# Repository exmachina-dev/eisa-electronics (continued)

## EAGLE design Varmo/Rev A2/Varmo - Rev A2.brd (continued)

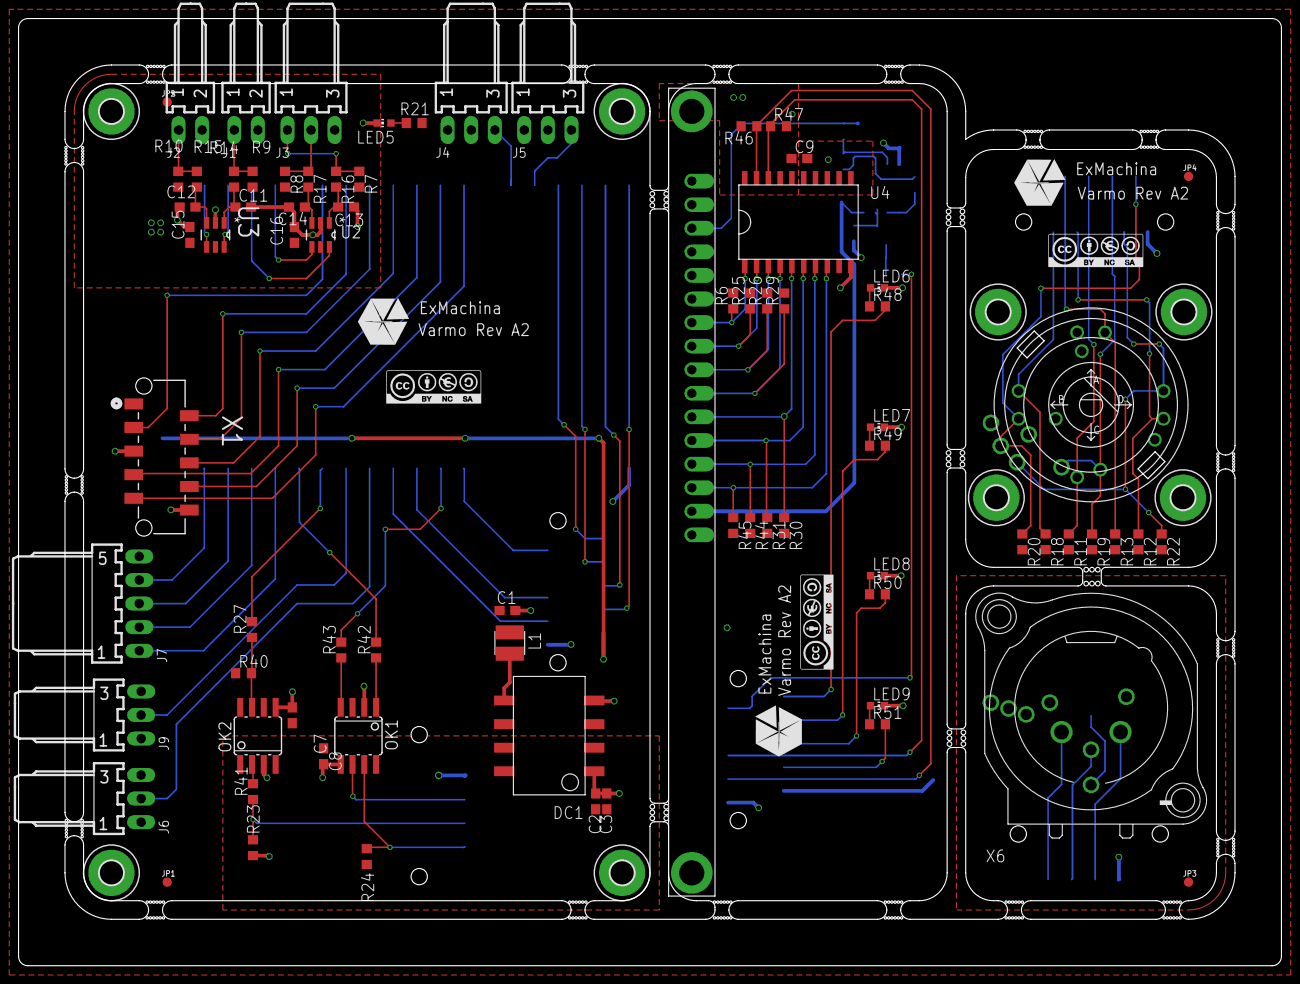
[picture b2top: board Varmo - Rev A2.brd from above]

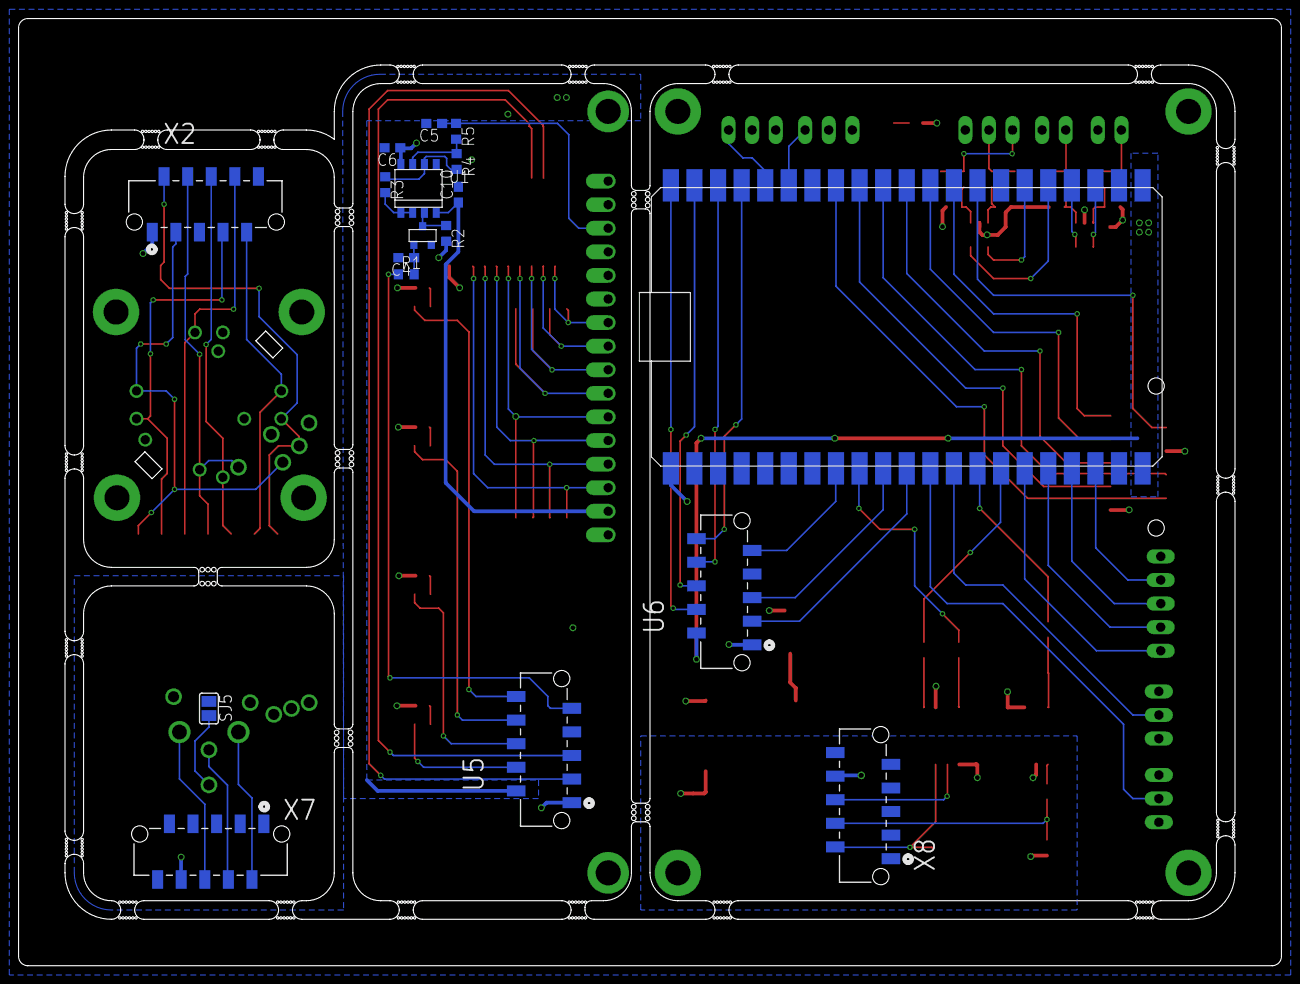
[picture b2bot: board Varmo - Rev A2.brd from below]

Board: 2 copper layers, 136.0 x 102.0 mm, 110 parts (18 on the bottom side), 74 nets.

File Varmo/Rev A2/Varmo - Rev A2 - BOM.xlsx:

Qty | Value | Device | Package | Parts | Description | MF | MPN | OC_FARNELL | OC_NEWARK | PACKAGE | SUPPLIER | VALUE
1 |  | SJ | SJ | SJ5 | SMD solder JUMPER |  |  |  | unknown
4 | 0.1uF | C-EUC0603 | C0603 | C4, C6, C9, C10 | CAPACITOR, European symbol |  | MC0603B104K160CT
9 | 0.1uF | C-EUC0603 | C0603 | C3, C7, C8, C11, C12, C13, C14, C15, C16 | CAPACITOR, European symbol |  | MC0603B104K160CT |  | 06R4923
1 | 1.5k | R-EU_R0603 | R0603 | R21 | RESISTOR, European symbol |  | MCMR06X1501FTL |  | 86T3542
1 | 100 | R-EU_R0603 | R0603 | R24 | RESISTOR, European symbol |  | MCMR06X1000FTL |  | 86T3500
1 | 100R | R-EU_R0603 | R0603 | R1 | RESISTOR, European symbol |  | MCMR06X1000FTL
1 | 10k | R-EU_R0603 | R0603 | R5 | RESISTOR, European symbol |  | MCMR06X1002FTL
7 | 1k | R-EU_R0603 | R0603 | R2, R3, R4, R48, R49, R50, R51 | RESISTOR, European symbol |  | MCMR06X1001FTL
4 | 1k | R-EU_R0603 | R0603 | R14, R15, R16, R17 | RESISTOR, European symbol |  | MCMR06X1001FTL |  | 86T3649
2 | 1k5 | R-EU_R0603 | R0603 | R27, R41 | RESISTOR, European symbol |  | MCMR06X1501FTL |  | 86T3500
2 | 22-05-7028-02 | 22-05-7028-02 |  | J1, J2 | CONNECTOR |  | 22-02-7038 | 9731601 | unknown
5 | 22-05-7038-03 | 22-05-7038-03 |  | J3, J4, J5, J6, J9 | CONNECTOR |  | 22-02-7038 | 9731610 | unknown
1 | 22-05-7058-05 | 22-05-7058-05 |  | J7 | CONNECTOR |  | 22-05-7038 | 9731636 | unknown
2 | 330 | R-EU_R0603 | R0603 | R42, R43 | RESISTOR, European symbol |  | MCMR06X3300FTL |  | 86T3500
1 | 4.7K | R-EU_R0603 | R0603 | R8 | RESISTOR, European symbol |  | MCMR06X4701FTL |  | 86T3649
10 | 4.7k | R-EU_R0603 | R0603 | R6, R25, R26, R29, R30, R31, R44, R45, R46, R47 | RESISTOR, European symbol |  | MCMR06X4701FTL
3 | 4.7k | R-EU_R0603 | R0603 | R7, R9, R10 | RESISTOR, European symbol |  | MCMR06X4701FTL |  | 86T3649
1 | 4.7uF | C-EUC0603 | C0603 | C5 | CAPACITOR, European symbol |  | MC0603X475K100CT
2 | 4.7uF | C-EUC0603 | C0603 | C1, C2 | CAPACITOR, European symbol |  | MC0603X475K100CT |  | 06X6198
1 | 47uH | 82473C | 8200 | L1 |  |  | 82473C |  | 40M7122 |  |  | 47uH
9 | 4k7 | R-EU_R0603 | R0603 | R11, R12, R13, R18, R19, R20, R22, R23, R40 | RESISTOR, European symbol |  | MCMR06X4701FTL |  | 86T3500
6 | 90814-0210 | 90814-0210 | MOLEX_90814-0210 | U5, U6, X1, X2, X7, X8 | CONN HEADER 10POS 1.27MM SMD TIN |  | 90814-0210 | 1757026 | 34R6217 | CONN-10POS | Molex
4 | Blue | LEDCHIP-LED0603 | CHIP-LED0603 | LED6, LED7, LED8, LED9 | LED |  | OVS-0603
3 | CC-BY-NC-SA | CC-BY-NC-SA | CC-BY-NC-SA | U$1, U$4, U$5
1 | EC20AE | EC20AE | EC20A | U$2 |  |  | EC20A1824401
3 | EXMACHINA-LOGO-NAME | EXMACHINA-LOGO-NAME | EXM-LOGO-BASELINE | U$3, U$6, U$7
4 | FIDUCIAL1X2 | FIDUCIAL1X2 | FIDUCIAL-1X2 | JP1, JP2, JP3, JP4 | Fiducial Alignment Points
1 | Green | LEDCHIP-LED0603 | CHIP-LED0603 | LED5 | LED |  | OVS-0604 |  | 15R2206
1 | HCPL0201 | HCPL0201 | SOIC08 | OK2 |  |  | HCPL-0201-500E
1 | HCPL0631 | HCPL0631 | SOIC08 | OK1 |  |  | HCPL-0631-500E
1 | LT1813CS8 | LT1813CS8 | SOIC8 | U1 | Dual AOP 3mA, 100MHz, 750V/us |  | LT1813CS8#PBF
1 | M20DX256 | M20DX256 | MK_CUSTOM | U8
1 | MC41605A12W | MC41605A12W | CONNECTOR | LCD1 |  |  | MC41605A12W-VNMLW
1 | MMBT2222AL | MMBT2222AL | SOT-23 | T1 | General Purpose Transistors |  | MMBT2222ALT1G
8 | MOUNT-PAD2.5 | MOUNT-PAD2.5 | P2.5 | MP1, MP2, MP3, MP4, MP5, MP6, MP7, MP8 | MOUNTING HOLE with drill center marker
1 | NC5MAV-SW | NC5MAV-SW | NC5MAV-SW | X6 | Neutrik Audio Connector XLR SERIES |  | NC5MAV-SW | unknown | 31M5714
1 | NTE0505MC | NTE0505MC | NTE | DC1 |  | C & D TECHNOLOGIES, INC | NTE0505MC |  | 61K3399
1 | PCA9665D | PCA9665D | SOT163-1 | U4
1 | RKJXTF42001 | RKJXTF42001 | RKJXT1F | ENC1 | 4-directional Stick Switch (with Encoder + Center-push Function)
2 | SN74LVC2G17DBVR | SN74LVC2G17DBVR | SOT95P280X145-6N | U2, U3 | DUAL SCHMITT-TRIGGER BUFFER | TEXAS INSTRUMENTS | SN74LVC2G17DBVR | 1470776 | 76C4207 | SOT-23-6 | Texas Instruments

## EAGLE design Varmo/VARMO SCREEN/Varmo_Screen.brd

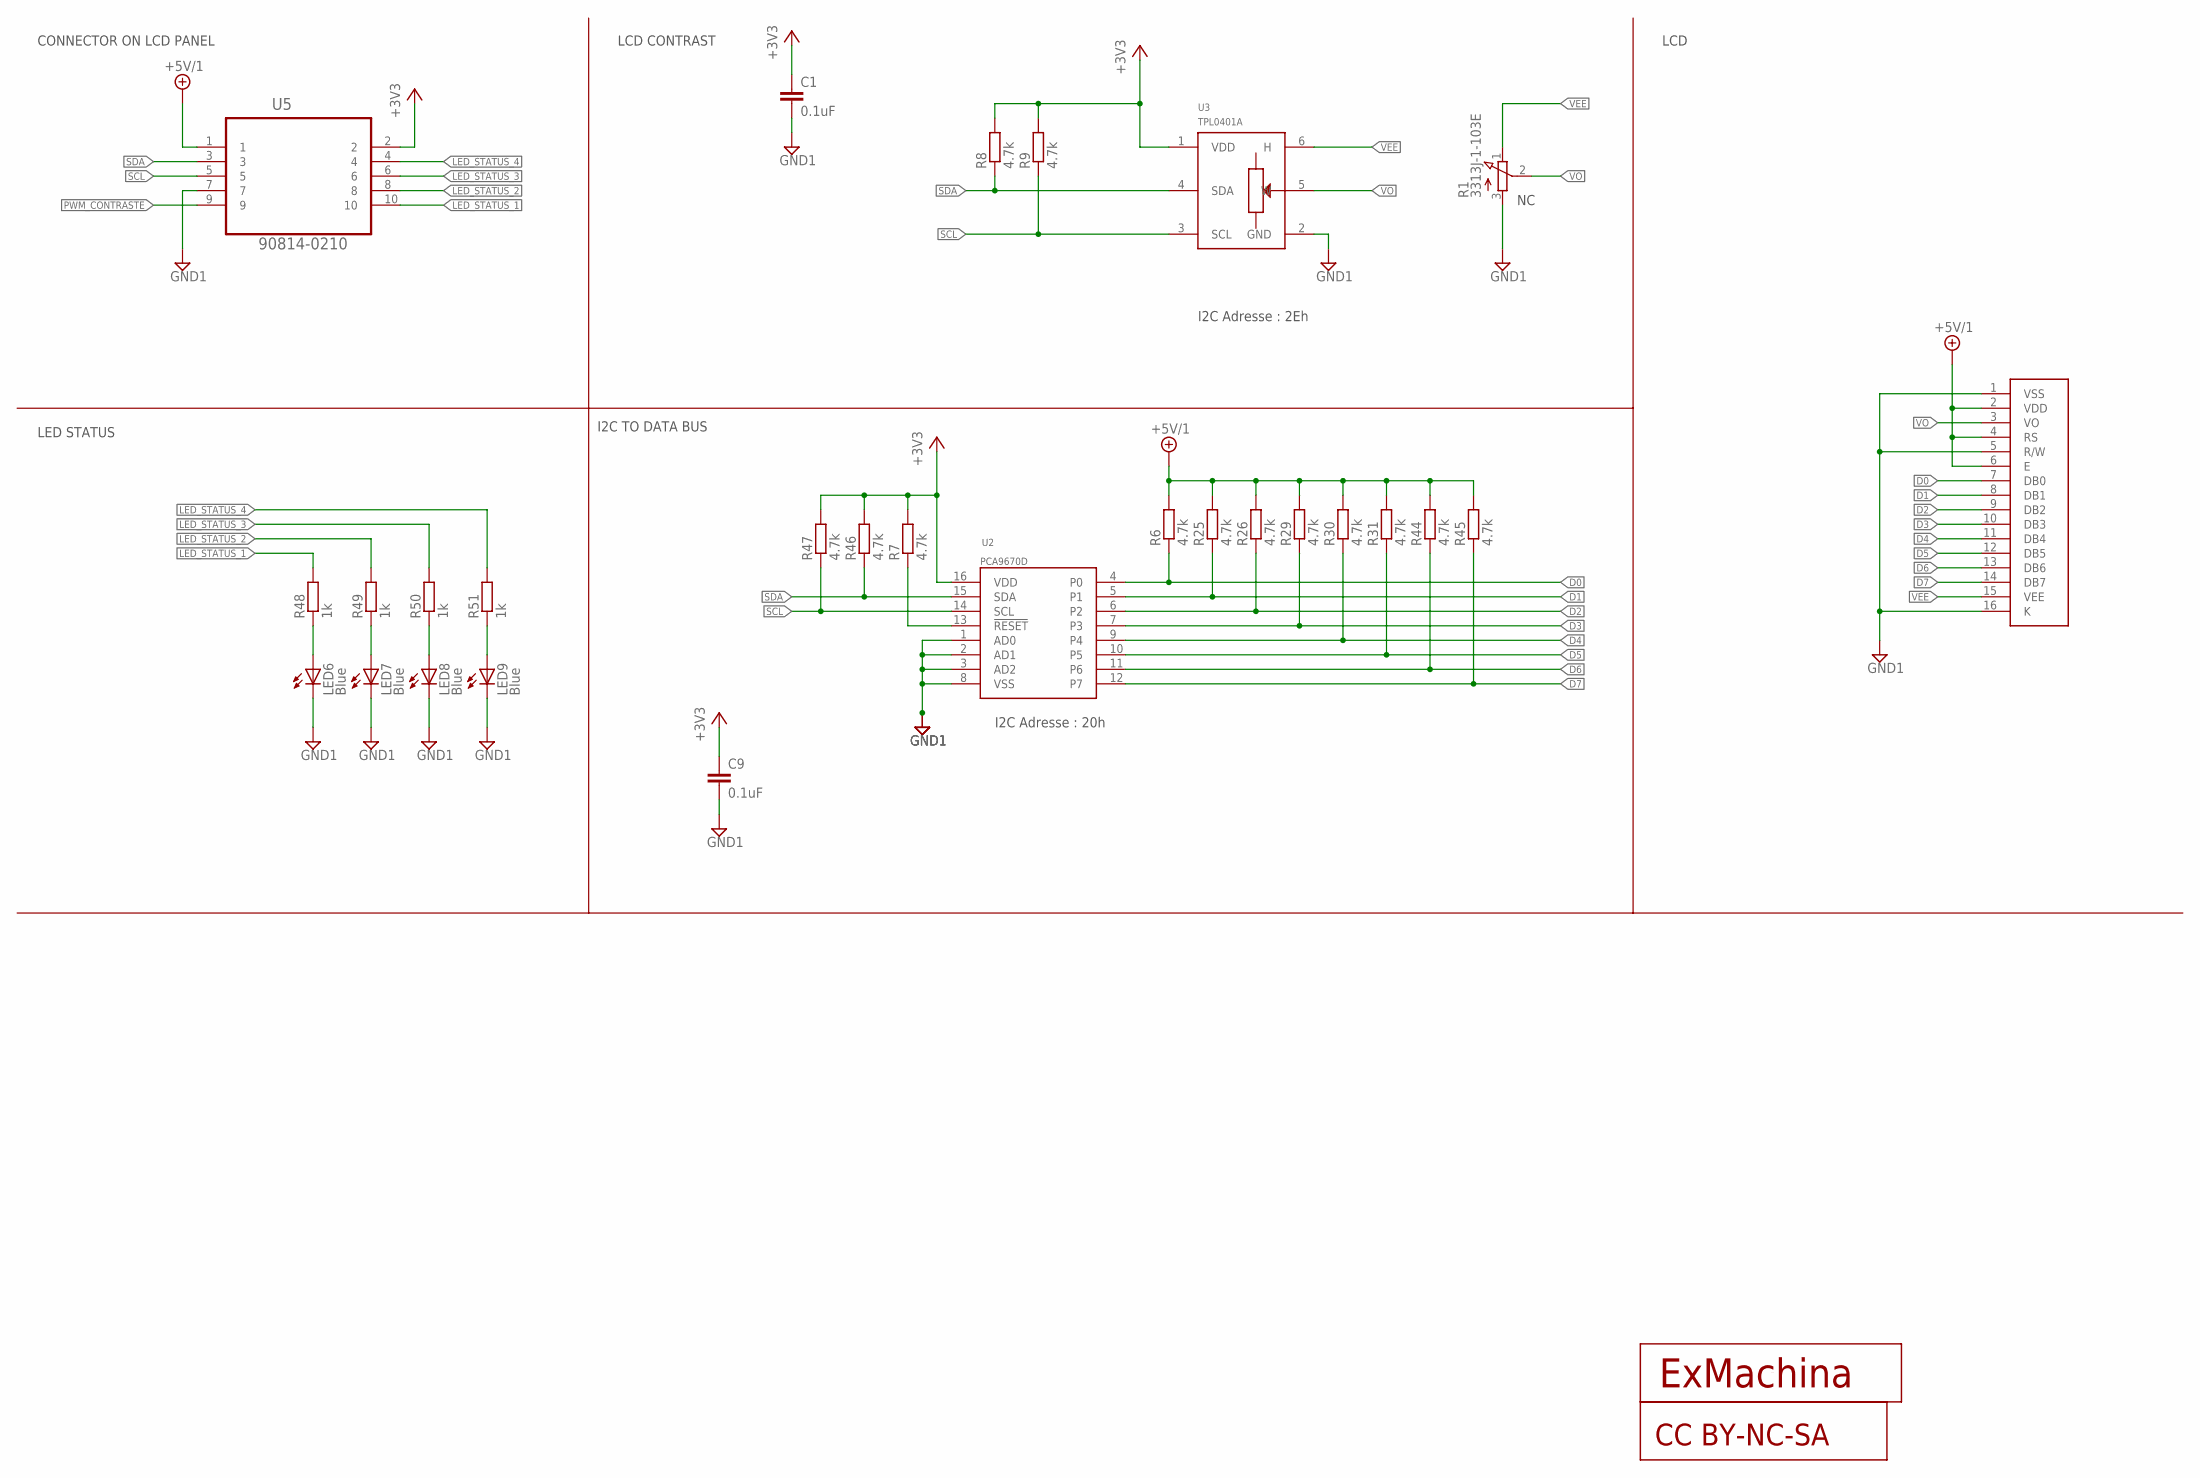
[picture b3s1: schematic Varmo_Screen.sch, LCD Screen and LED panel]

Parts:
C1, C9: 0.1uF; C0603
LCD1: MC41605A12W; CONNECTOR
LED6, LED7, LED8, LED9: Blue; CHIP-LED0603
R1: 3313J-1-103E; 3313J
R6, R7, R8, R9, R25, R26, R29, R30, R31, R44, R45, R46, R47: 4.7k; R0603
R48, R49, R50, R51: 1k; R0603
U2: PCA9670D; SOT162-1
U3: TPL0401A; SC-70-DCK
U5: 90814-0210; MOLEX_90814-0210
U$5: CC-BY-NC-SA
U$7: EXMACHINA-LOGO-NAME; EXM-LOGO-BASELINE

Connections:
+3V3: C1.1, C9.1, R7.2, R8.2, R9.2, R46.2, R47.2, U2.16 (VDD), U3.1 (VDD), U5.2
+5V/1: LCD1.2 (VDD), LCD1.4 (RS), LCD1.6 (E), R6.2, R25.2, R26.2, R29.2, R30.2, R31.2, R44.2, R45.2, U5.1
D0: LCD1.7 (DB0), R6.1, U2.4 (P0)
D1: LCD1.8 (DB1), R25.1, U2.5 (P1)
D2: LCD1.9 (DB2), R26.1, U2.6 (P2)
D3: LCD1.10 (DB3), R29.1, U2.7 (P3)
D4: LCD1.11 (DB4), R30.1, U2.9 (P4)
D5: LCD1.12 (DB5), R31.1, U2.10 (P5)
D6: LCD1.13 (DB6), R44.1, U2.11 (P6)
D7: LCD1.14 (DB7), R45.1, U2.12 (P7)
GND1: C1.2, C9.2, LCD1.1 (VSS), LCD1.5 (R/W), LCD1.16 (K), LED6.C, LED7.C, LED8.C, LED9.C, R1.3 (A), U2.1 (AD0), U2.2 (AD1), U2.3 (AD2), U2.8 (VSS), U3.2 (GND), U5.7
LED_STATUS_1: R48.2, U5.10
LED_STATUS_2: R49.2, U5.8
LED_STATUS_3: R50.2, U5.6
LED_STATUS_4: R51.2, U5.4
unnamed: R7.1, U2.13 (!RESET)
unnamed: LED6.A, R48.1
unnamed: LED7.A, R49.1
unnamed: LED8.A, R50.1
unnamed: LED9.A, R51.1
PWM_CONTRASTE: U5.9
SCL: R9.1, R47.1, U2.14 (SCL), U3.3 (SCL), U5.5
SDA: R8.1, R46.1, U2.15 (SDA), U3.4 (SDA), U5.3
VEE: LCD1.15 (VEE), R1.1 (E), U3.6 (H)
VO: LCD1.3 (VO), R1.2 (S), U3.5 (W)

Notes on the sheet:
LCD CONTRAST
CONNECTOR ON LCD PANEL
LED STATUS
I2C TO DATA BUS
LCD
I2C Adresse : 20h
I2C Adresse : 2Eh

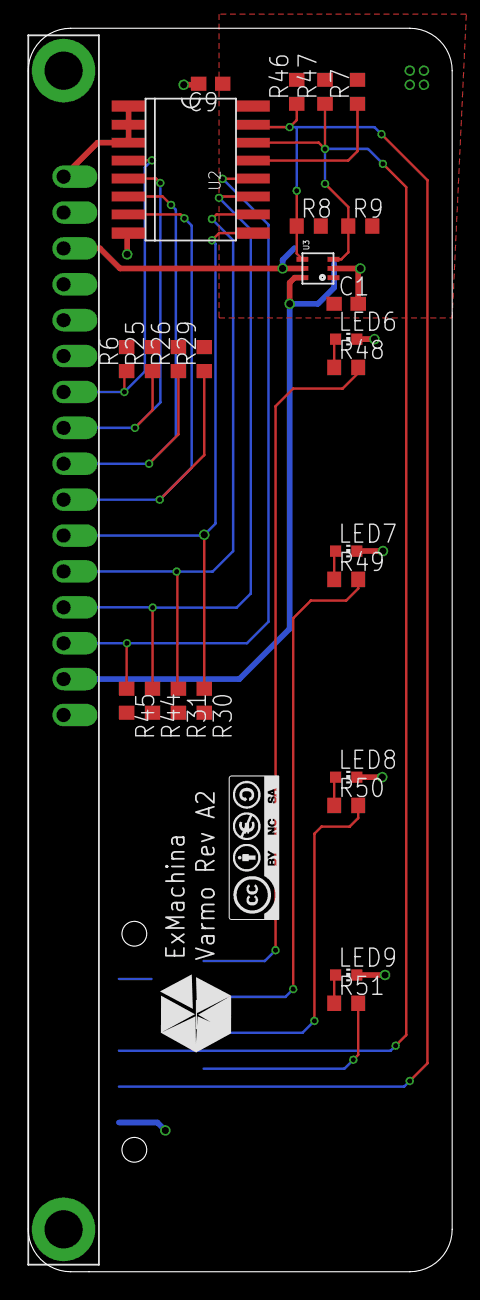
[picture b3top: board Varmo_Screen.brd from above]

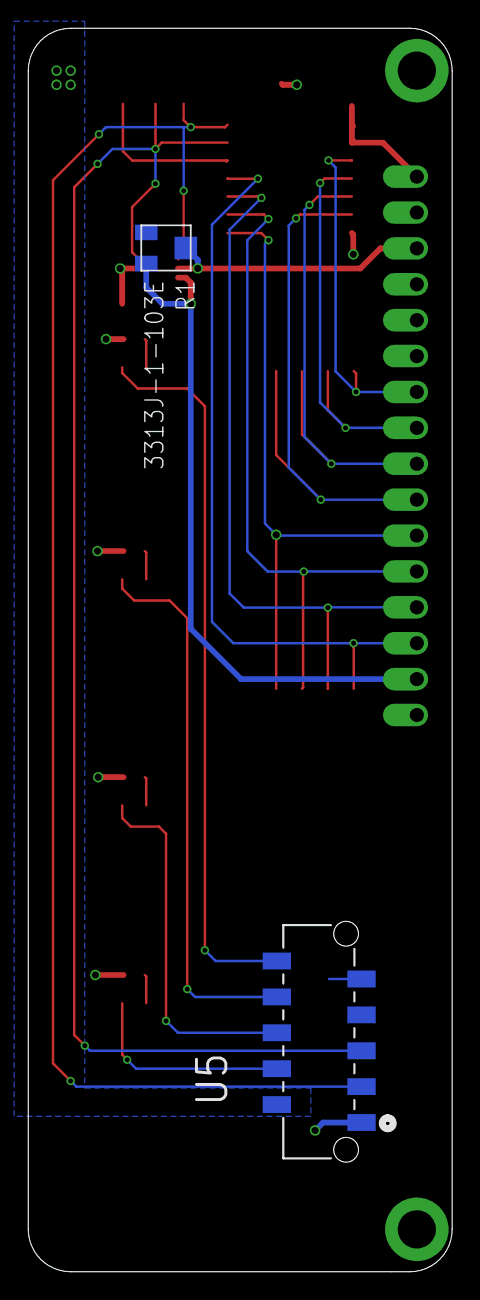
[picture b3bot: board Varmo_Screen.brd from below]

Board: 2 copper layers, 30.0 x 88.0 mm, 30 parts (2 on the bottom side), 24 nets.

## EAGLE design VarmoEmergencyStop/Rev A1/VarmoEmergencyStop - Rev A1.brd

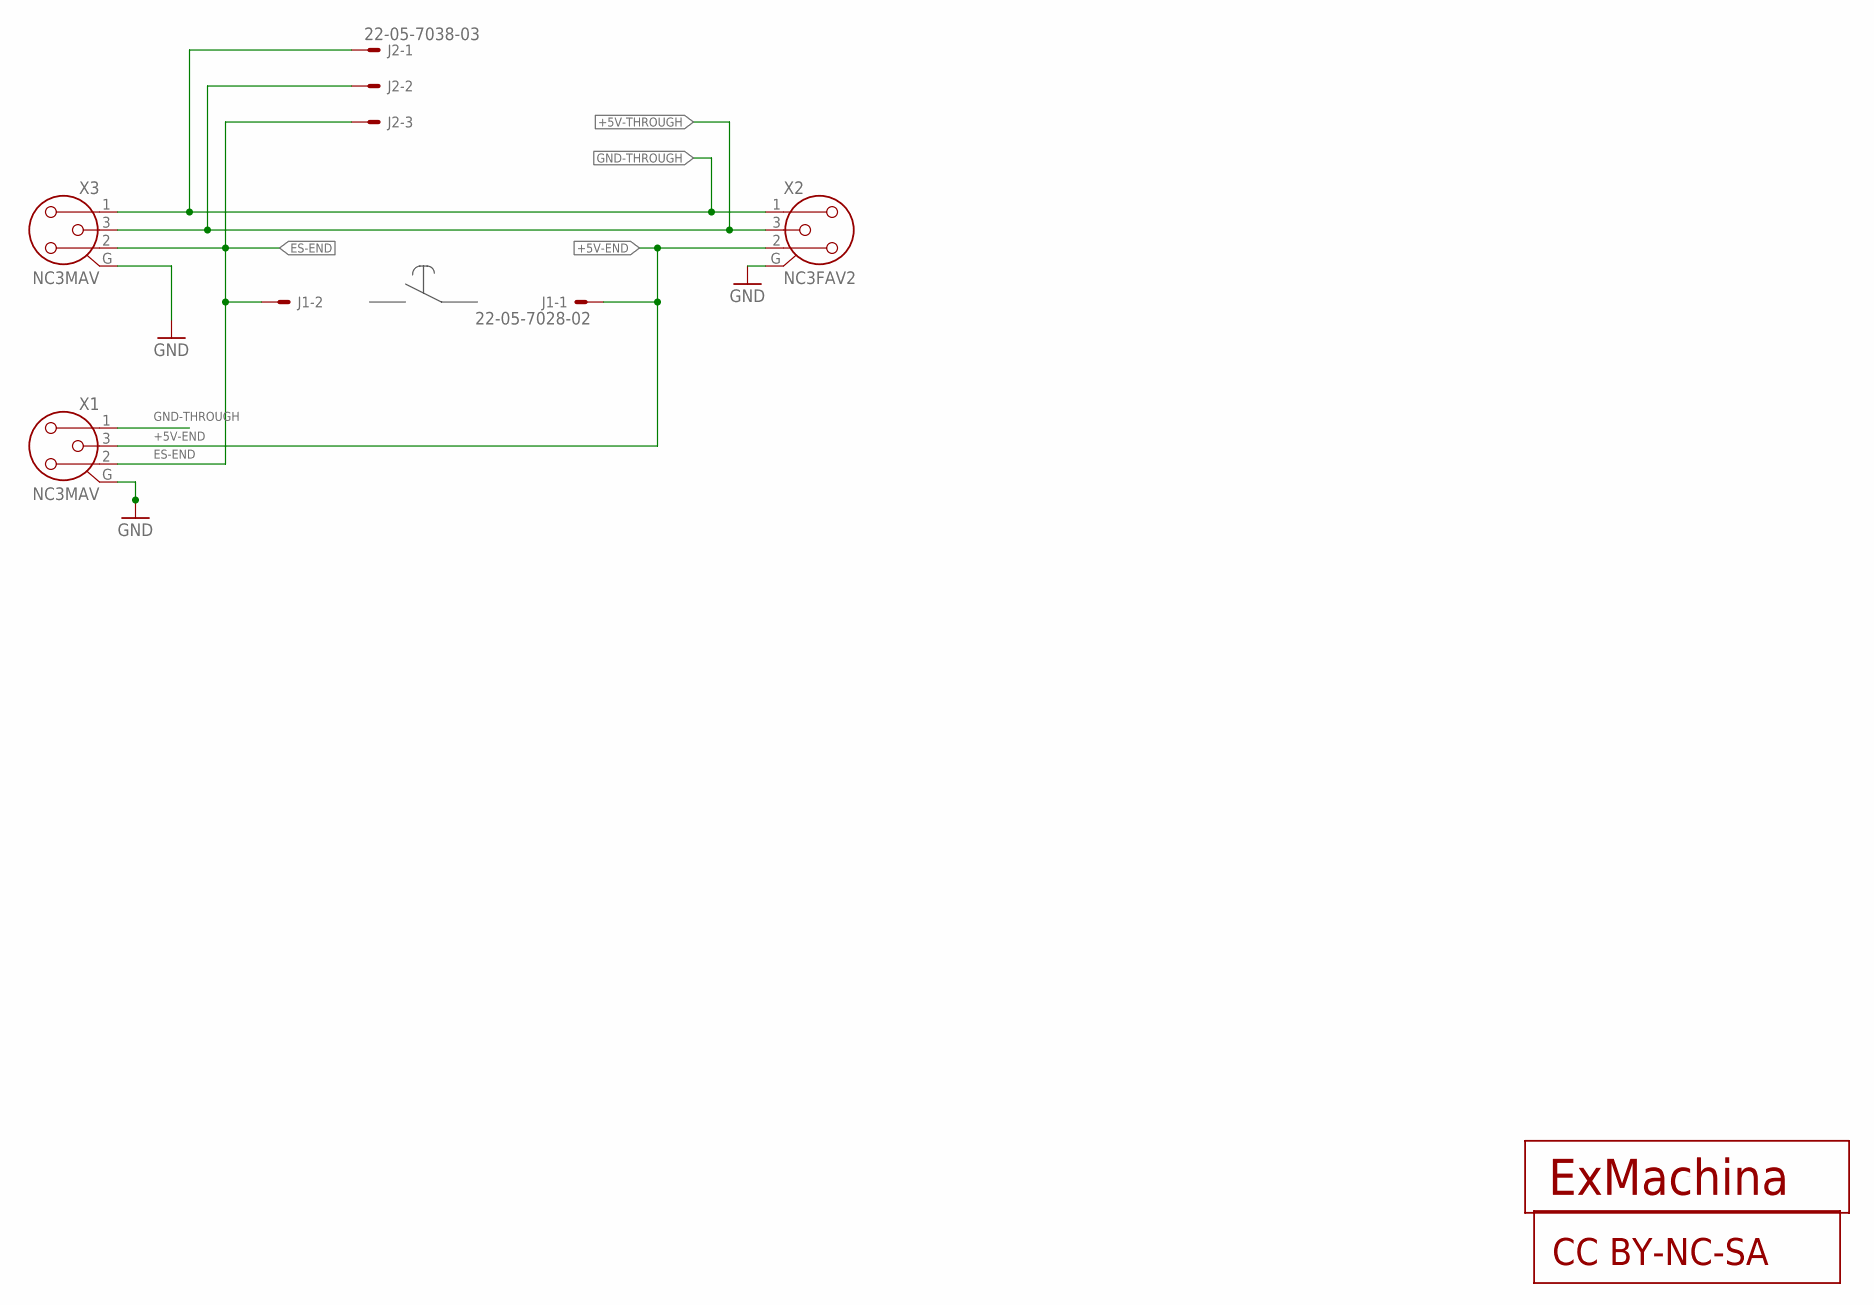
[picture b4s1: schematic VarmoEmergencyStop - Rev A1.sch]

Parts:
J1: 22-05-7028-02; 7395-02
J2: 22-05-7038-03; 7395-03
U$1: EXMACHINA-LOGO-NAME; EXM-LOGO-BASELINE
U$2: CC-BY-NC-SA
X1, X3: NC3MAV
X2: NC3FAV2

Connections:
+5V-END: J1.1, X1.3, X2.2
+5V-THROUGH: J2.2, X2.3, X3.3
ES-END: J1.2, J2.3, X1.2, X3.2
GND: X1.G, X2.G, X3.G
GND-THROUGH: J2.1, X1.1, X2.1, X3.1

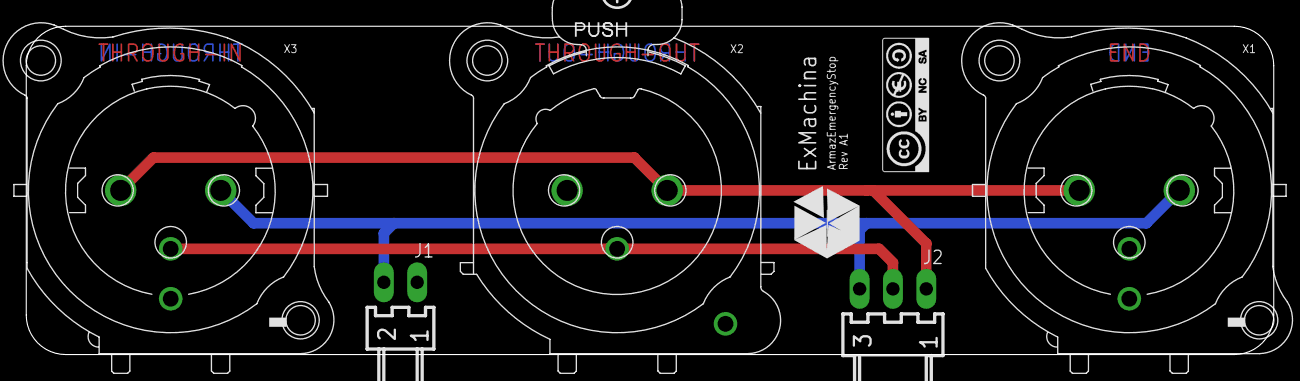
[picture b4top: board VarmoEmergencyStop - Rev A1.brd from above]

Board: 2 copper layers, 95.0 x 25.0 mm, 7 parts (0 on the bottom side), 5 nets.

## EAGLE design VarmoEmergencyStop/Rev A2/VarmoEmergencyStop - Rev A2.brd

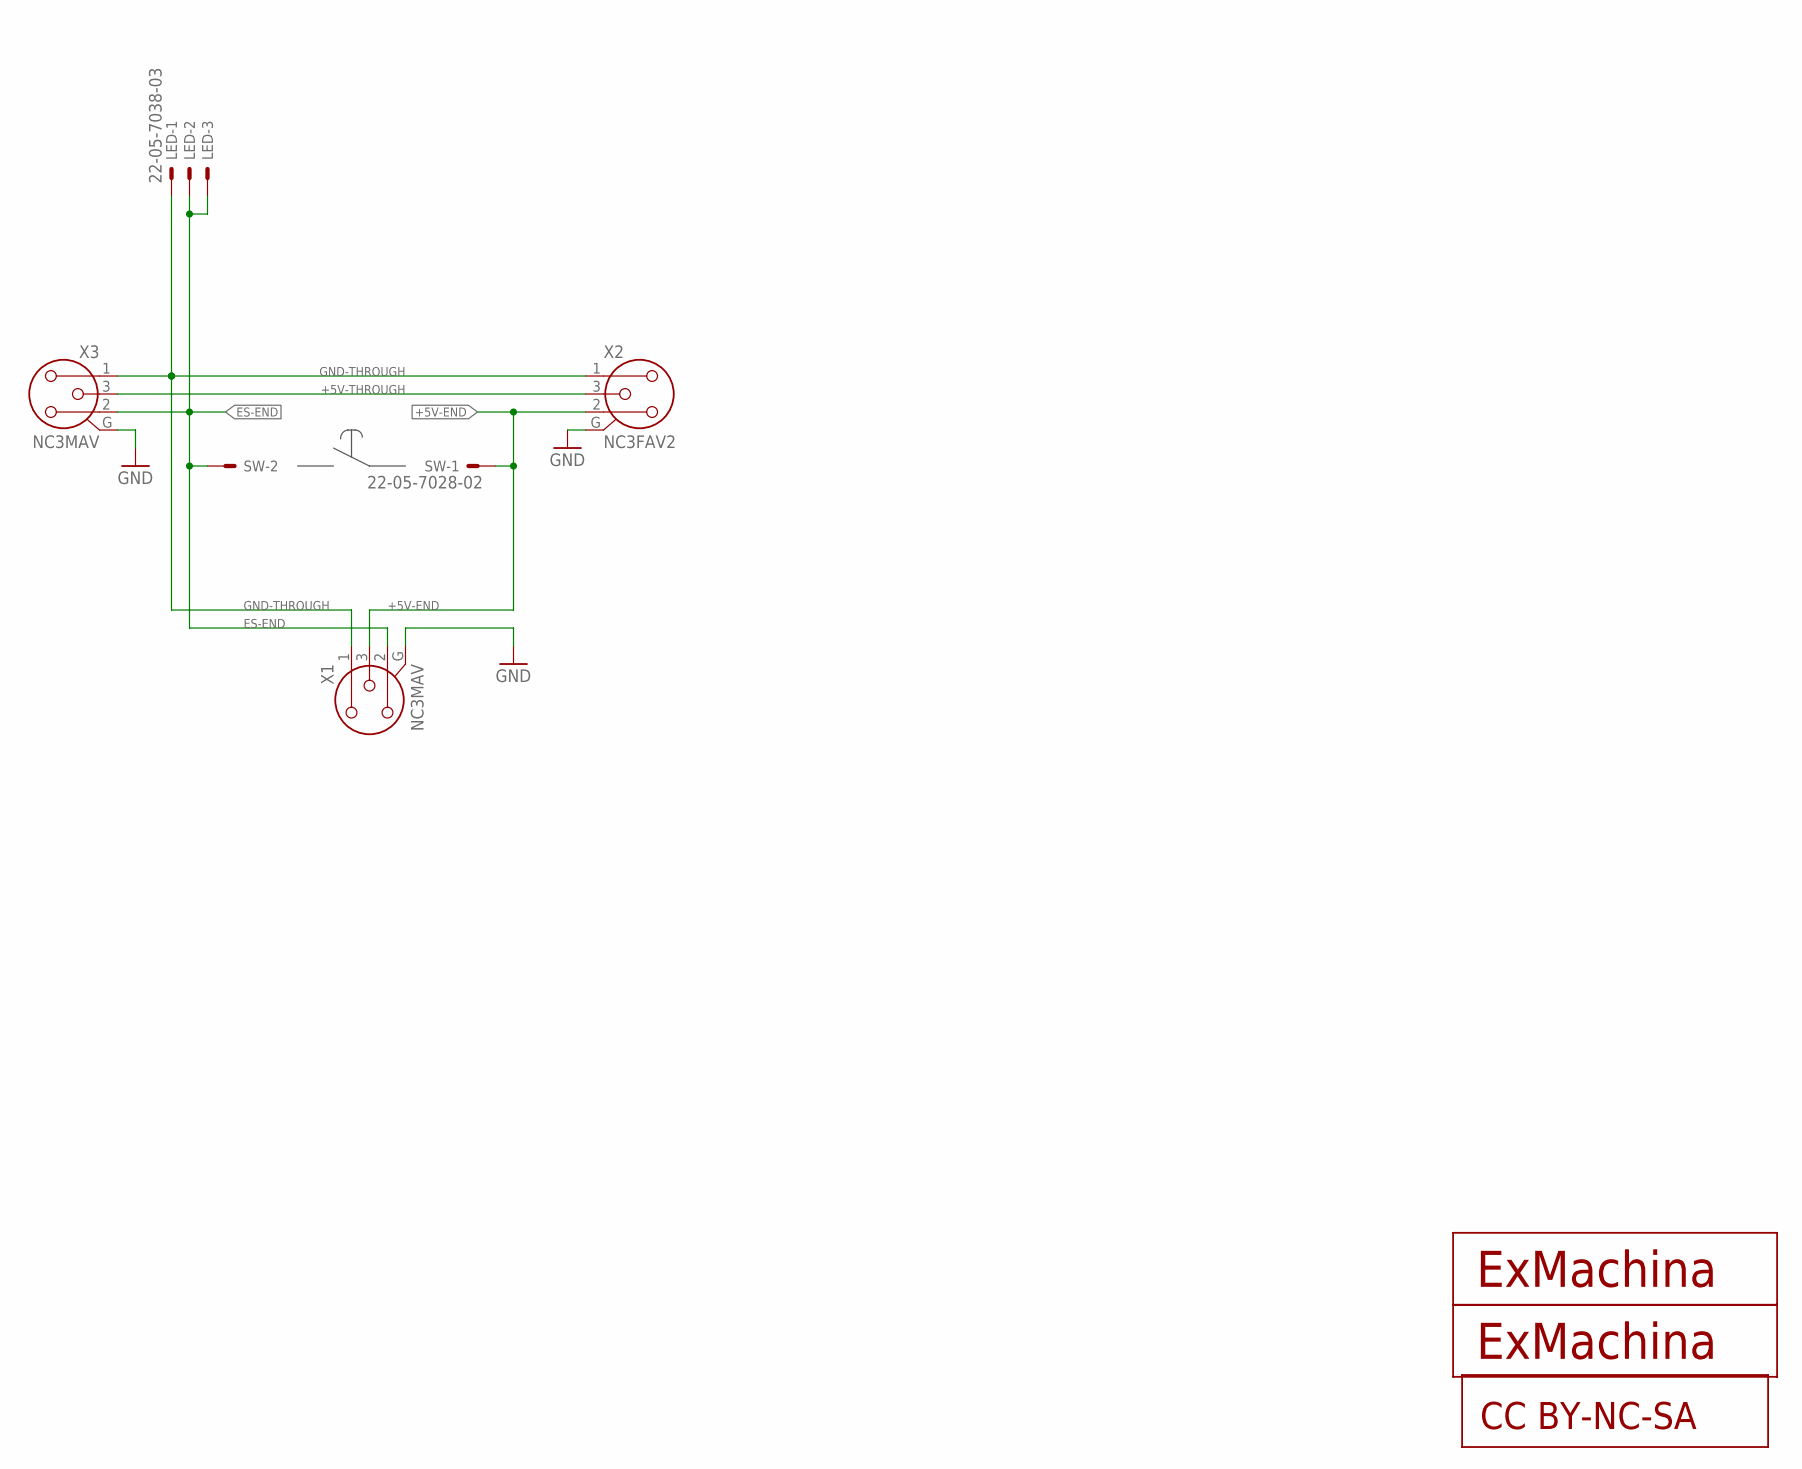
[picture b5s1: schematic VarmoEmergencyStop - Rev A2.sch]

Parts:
LED: 22-05-7038-03; 7395-03
SW: 22-05-7028-02; 7395-02
U$1, U$3: EXMACHINA-LOGO-NAME; EXM-LOGO-BASELINE
U$2: CC-BY-NC-SA
X1, X3: NC3MAV
X2: NC3FAV2

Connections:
+5V-END: SW.1, X1.3, X2.2
+5V-THROUGH: X2.3, X3.3
ES-END: LED.2, LED.3, SW.2, X1.2, X3.2
GND: X1.G, X2.G, X3.G
GND-THROUGH: LED.1, X1.1, X2.1, X3.1

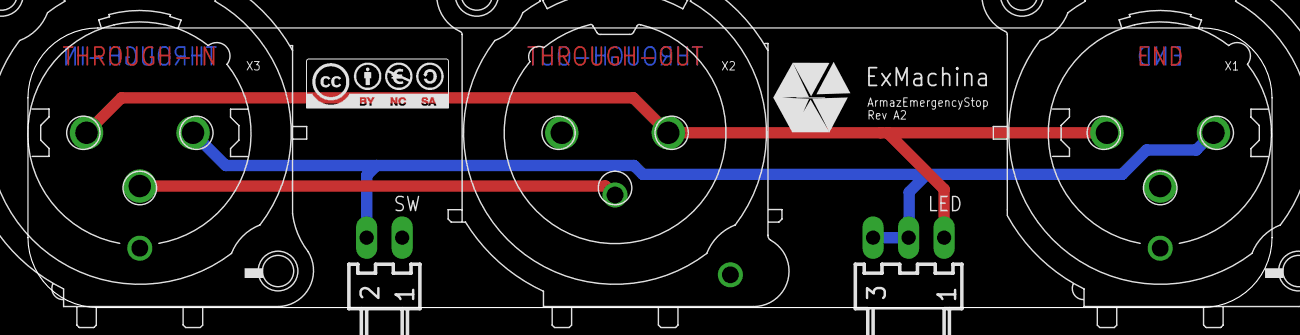
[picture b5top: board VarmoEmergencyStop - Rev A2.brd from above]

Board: 2 copper layers, 89.0 x 20.0 mm, 8 parts (1 on the bottom side), 5 nets.

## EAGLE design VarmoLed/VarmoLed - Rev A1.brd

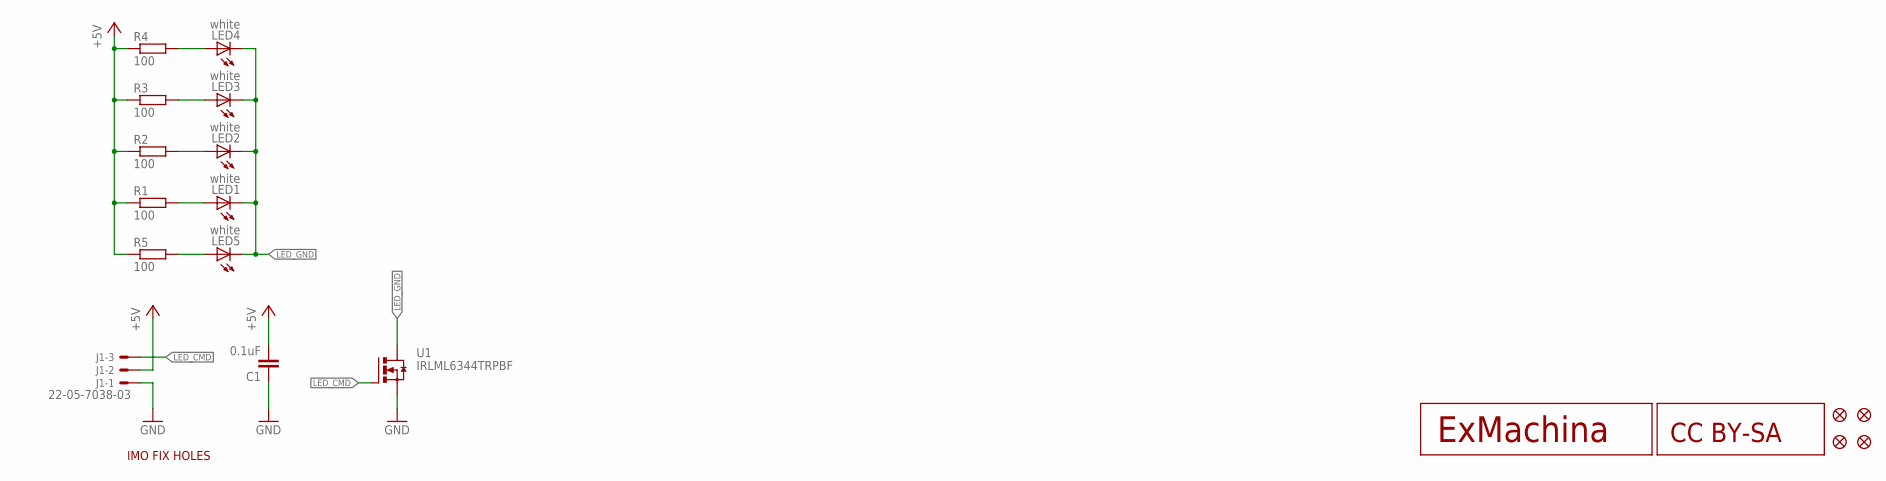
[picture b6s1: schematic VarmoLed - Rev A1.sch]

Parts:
C1: 0.1uF; C0603
J1: 22-05-7038-03; 7395-03
JP1, JP2, JP3, JP4: FIDUCIAL1X2; FIDUCIAL-1X2
LED1, LED2, LED3, LED4, LED5: white; CHIP-LED0603
R1, R2, R3, R4, R5: 100; R0603
U1: IRLML6344TRPBF; SOT95P240X112-3N
U$1: IMO-FIXHOLES
U$2: EXMACHINA-LOGO-NAME; EXM-LOGO-BASELINE
U$3: CC-BY-SA

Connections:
+5V: C1.2, J1.2, R1.1, R2.1, R3.1, R4.1, R5.1
GND: C1.1, J1.1, U1.2 (S)
LED_CMD: J1.3, U1.1 (G)
LED_GND: LED1.C, LED2.C, LED3.C, LED4.C, LED5.C, U1.3 (D)
unnamed: LED1.A, R1.2
unnamed: LED2.A, R2.2
unnamed: LED3.A, R3.2
unnamed: LED4.A, R4.2
unnamed: LED5.A, R5.2

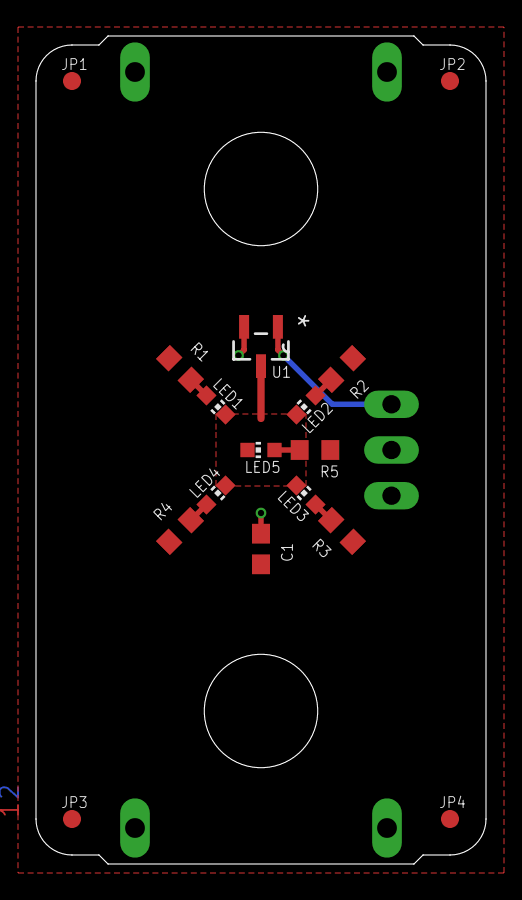
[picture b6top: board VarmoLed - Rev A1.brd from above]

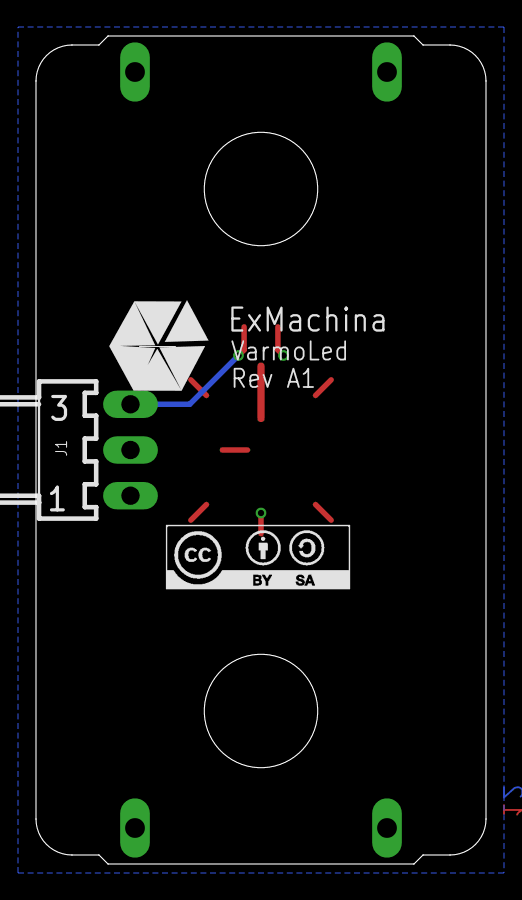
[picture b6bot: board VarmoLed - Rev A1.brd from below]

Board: 2 copper layers, 25.0 x 46.0 mm, 20 parts (3 on the bottom side), 9 nets.
